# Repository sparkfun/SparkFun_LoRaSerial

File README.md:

SparkFun LoRaSerial
========================================

[*SparkFun LoRaSerial Kit - 915MHz (WRL-19311)*](https://www.sparkfun.com/products/19311)

Head to the [LoRaSerial Product Manual](http://docs.sparkfun.com/SparkFun_LoRaSerial/) for technical documentation.

LoRaSerial is a pair of serial radio modems that simply passes serial back and forth. Do you have a system that needs to report data every few seconds? Is it located beyond WiFi or Bluetooth range? Do you need 9 mile/15 kilometer range? LoRaSerial transmits data over LoRa giving it incredible range compared to other methods. We’ve regularly transmitted over 9 miles/15km line-of-sight using two LoRaSerial radios, right out of the box.

LoRaSerial utilizes a 1 watt 915MHz transceiver and an open source protocol to and transmit AES encrypted data at 4800bps or approximately 480 bytes per second. Video streaming, this is not. LoRaSerial is very good at getting whatever data you need from point A to point B, encrypted, without configuration. The radios automatically frequency hop (FHSS) between channels to avoid collisions. The ‘airspeed’ or data rate is configurable up to approximately 2,000 bytes per second for shorter range, or for *extremely* long range transmissions, as low as 400 bytes per second.

LoRaSerial radios support simple point to point and point as well as multipoint broadcasts. Multipoint broadcasting makes it ideal for GNSS RTK and many other scenarios where one device needs to produce data and many devices need to consume that data.

The LoRaSerial firmware supports an innovative and simple to use ‘training’ method. Pressing the train button on both radios will generate a new random network ID and AES encryption key and share them between radios. This makes pairing radios in the field as simple as a button press. WiFi WPS this is not. Bring the radios near each other and the LoRaSerial training method is simple and secure.

Currently, SparkFun is offering radios utilizing 915MHz modems that are allowed in most parts of the world. Please check your local restrictions. The radios are fully configurable to restrict frequencies, channels, dwell time, power output, and a variety of other settings to make the radios compatible with your local regulations.

Repository Contents
-------------------

* **/Binaries** - Compiled firmware, ready to load
* **/Documents** - Datasheets and additional product information
* **/Firmware** - Main Arduino firmware
* **/Hardware** - Eagle PCB files

Documentation
--------------

* **[LoRaSerial Product Manual](http://docs.sparkfun.com/SparkFun_LoRaSerial/)** - Configuration guide for the SparkFun LoRaSerial.

License Information
-------------------

This product is _**open source**_! 

Please review the LICENSE.md file for license information. 

If you have any questions or concerns on licensing, please contact technical support on our [SparkFun forums](https://forum.sparkfun.com/viewforum.php?f=152).

Distributed as-is; no warranty is given.

- Your friends at SparkFun.

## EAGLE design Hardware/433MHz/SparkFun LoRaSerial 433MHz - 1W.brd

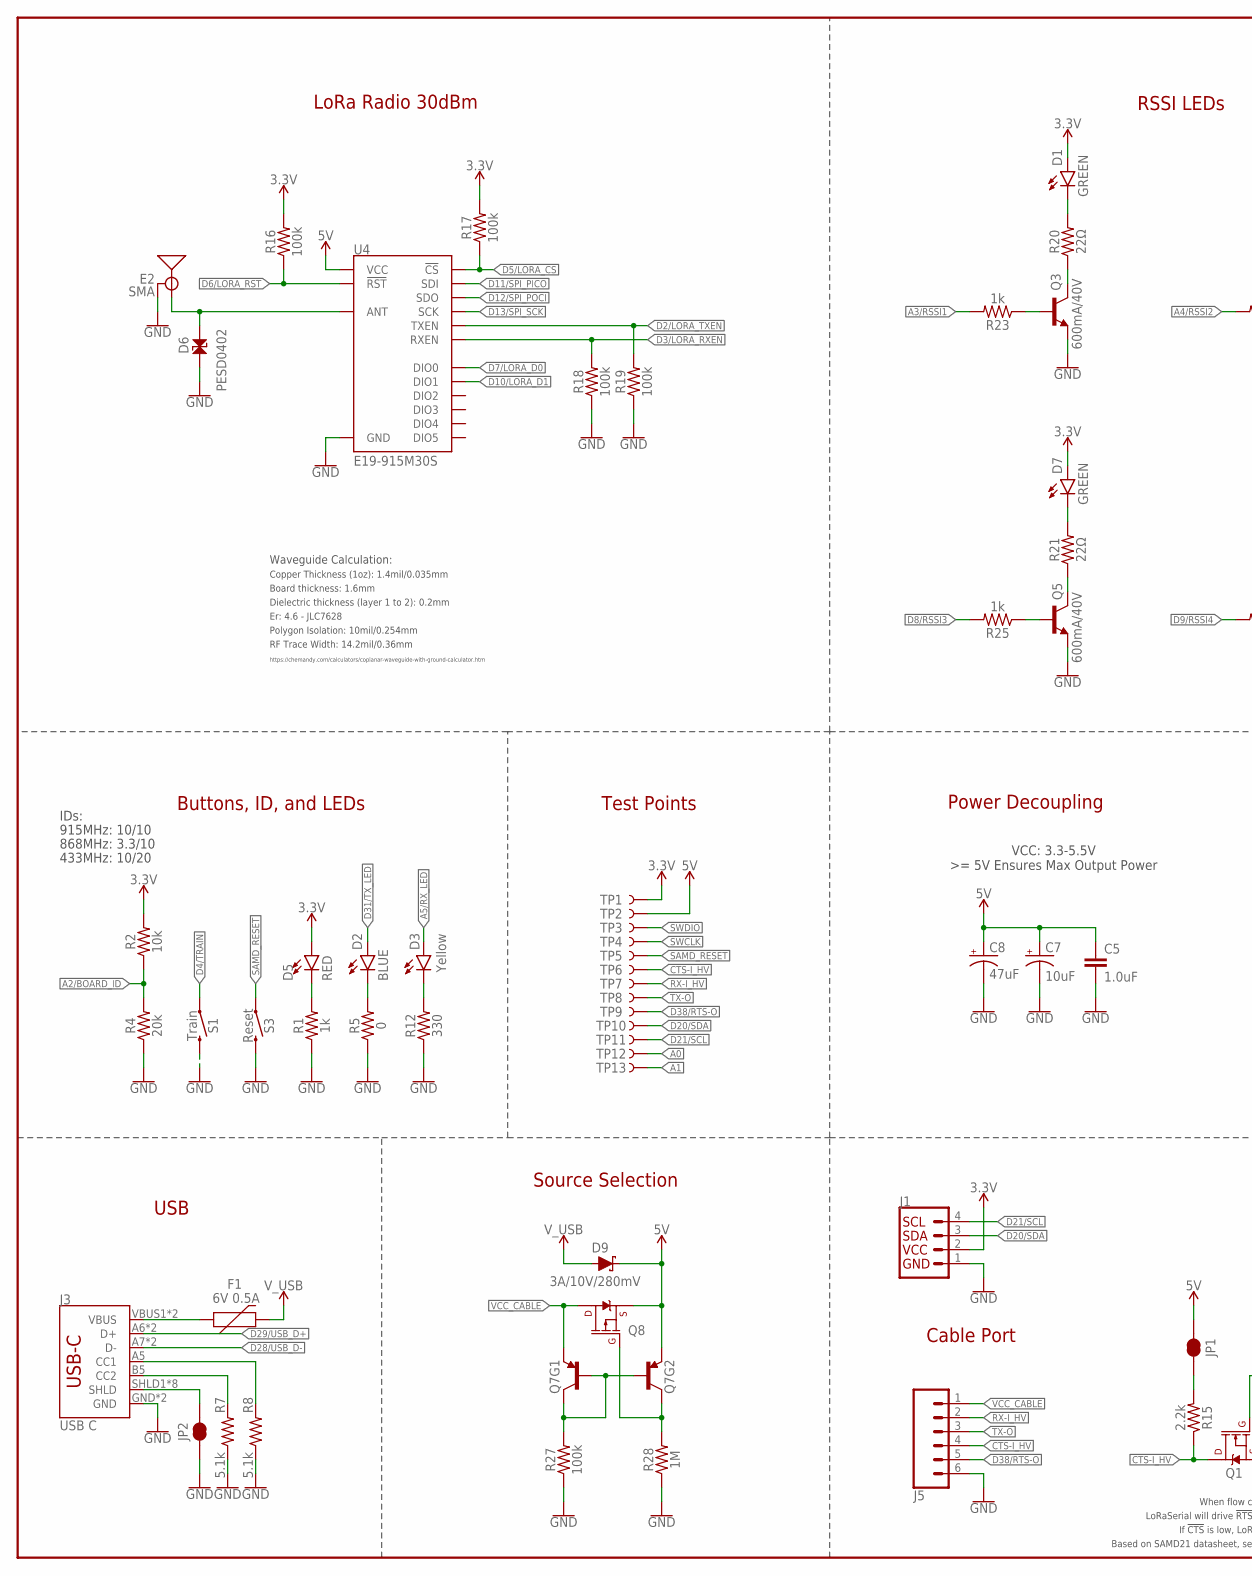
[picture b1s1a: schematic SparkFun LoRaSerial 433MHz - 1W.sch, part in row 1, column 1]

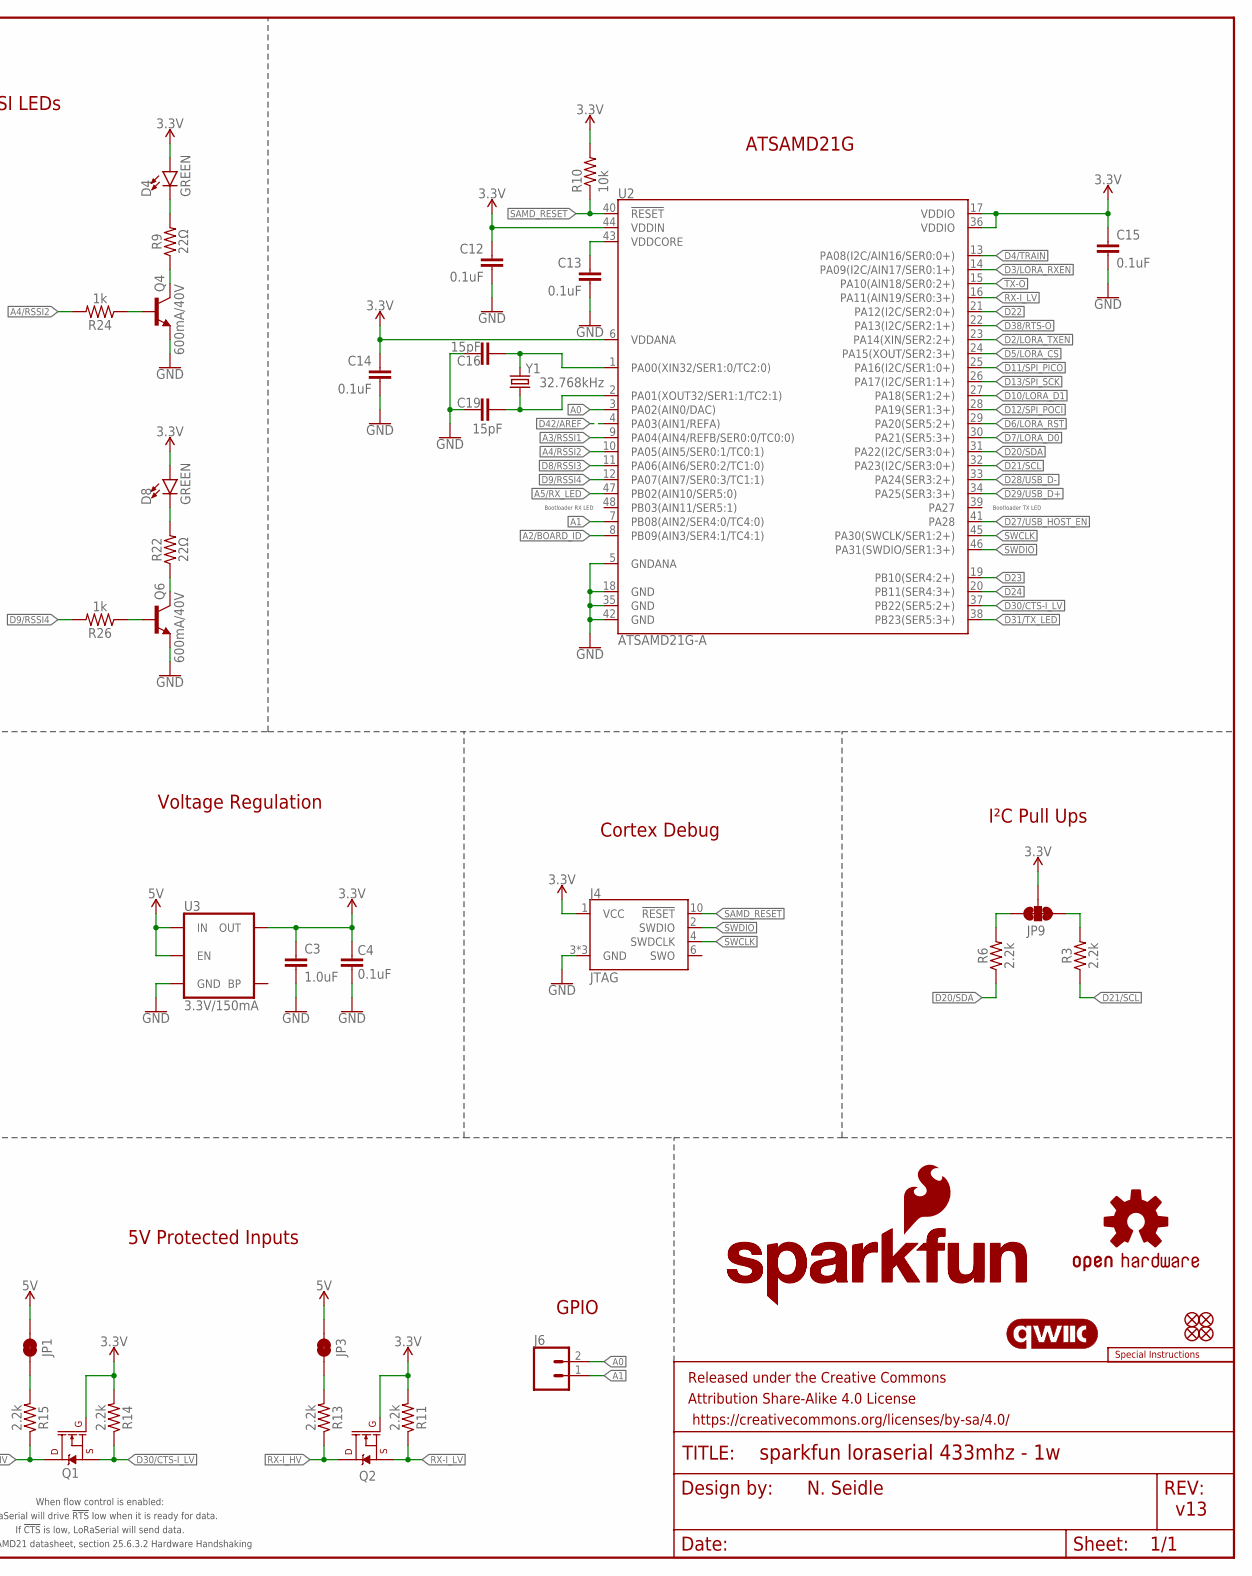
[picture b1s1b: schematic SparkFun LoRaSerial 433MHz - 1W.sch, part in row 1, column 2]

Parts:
C3, C5: 1.0uF; 0603
C4, C12, C13, C14, C15: 0.1uF; 0603
C7: 10uF; EIA3216
C8: 47uF; EIA3528
C16, C19: 15pF; 0603
D1, D4, D7, D8: GREEN; LED-0603
D2: BLUE; LED-0603
D3: Yellow; LED-0603
D5: RED; LED-0603
D6: PESD0402; 0402-TIGHT
D9: 3A/10V/280mV; SOD-323
E2: SMA; SMA-EDGE
F1: 6V 0.5A; 0805
FID1, FID2, FID3, FID4: FIDUCIAL1X2; FIDUCIAL-1X2
FRAME3: FRAME-LEDGER; CREATIVE_COMMONS
J1: QWIIC_RIGHT_ANGLE; JST04_1MM_RA
J3: USB C; USB-C-16P
J4: JTAG; 2X5-PTH-1.27MM-NO_SILK
J5: CONN_06JST-SMD-LOCKING; JST-6-SMD-1.25MM-LOCKING
J6: CONN_021X02_NO_SILK; 1X02_NO_SILK
JP1, JP2, JP3: JUMPER-SMT_2_NC_TRACE_SILK; SMT-JUMPER_2_NC_TRACE_SILK
JP9: JUMPER-SMT_3_2-NC_TRACE_SILK; SMT-JUMPER_3_2-NC_TRACE_SILK
LOGO1: SPECIAL_INSTRUCTIONS-ORDERING; ORDERING_INSTRUCTIONS
LOGO2: SFE_LOGO_NAME_FLAME9_MM; SFE_LOGO_NAME_FLAME_9MM
LOGO3: QWIIC_LOGO_CONNECTOR; QWIIC_5.5MM
LOGO4: OSHW-LOGOMINI; OSHW-LOGO-MINI
LOGO5: SFE_LOGO_NAME9_MM; SFE_LOGO_NAME_9MM
Q1, Q2: 20V/0.2A/8MHz/1.2Ω/1Vth; SOT-416FL
Q3, Q4, Q5, Q6: 600mA/40V; SOT23-3
Q7: TRANS_PNP_DUALSOT-363; SOT363_PHILIPS
Q8: 20V/4.2A/52mΩ/1.4W; SOT23-3
R1, R23, R24, R25, R26: 1k; 0603
R2, R10: 10k; 0603
R3, R6, R11, R13, R14, R15: 2.2k; 0603
R4: 20k; 0603
R5: 0; 0603
R7, R8: 5.1k; 0603
R9, R20, R21, R22: 22Ω; 0603
R12: 330; 0603
R16, R17, R18, R19, R27: 100k; 0603
R28: 1M; 0603
S1: Train; TACTILE_SWITCH_SMD_RIGHT_ANGLE
S3: Reset; TACTILE_SWITCH_SMD_5.2MM
TP1, TP2, TP3, TP4, TP5, TP6, TP7, TP8, TP9, TP10, TP11, TP12, TP13: TEST-POINT3X5; PAD.03X.05
U2: ATSAMD21G-A; TQFP-48
U3: 3.3V/150mA; SOT23-5
U4: E19-915M30S; E19-433M30S
Y1: 32.768kHz; CRYSTAL-SMD-3.2X1.5MM

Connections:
3.3V: C3.1, C4.2, C12.1, C14.1, C15.1, D1.A, D4.A, D5.A, D7.A, D8.A, J1.2, J4.1 (VCC), JP9.2, Q1.1 (G), Q2.1 (G), R2.2, R10.2, R11.2, R14.2, R16.2, R17.2, TP1.1, U2.6 (VDDANA), U2.17 (VDDIO), U2.36 (VDDIO), U2.44 (VDDIN), U3.5 (OUT)
5V: C5.1, C7.+, C8.A (+), D9.C, JP1.2, JP3.2, Q7.4 (E), Q8.2 (S), TP2.1, U3.1 (IN), U3.3 (EN), U4.11 (VCC)
!CTS!-I_HV: J5.4, Q1.3 (D), R15.1, TP6.1
A0: J6.2, TP12.1, U2.3 (PA02(AIN0/DAC))
A1: J6.1, TP13.1, U2.7 (PB08(AIN2/SER4:0/TC4:0))
A2/BOARD_ID: R2.1, R4.2, U2.8 (PB09(AIN3/SER4:1/TC4:1))
A3/RSSI1: R23.2, U2.9 (PA04(AIN4/REFB/SER0:0/TC0:0))
A4/RSSI2: R24.2, U2.10 (PA05(AIN5/SER0:1/TC0:1))
A5/RX_LED: D3.A, U2.47 (PB02(AIN10/SER5:0))
CC1: J3.A5 (CC1), R8.2
CC2: J3.B5 (CC2), R7.2
D2/LORA_TXEN: R19.2, U2.23 (PA14(XIN/SER2:2+)), U4.16 (TXEN)
D3/LORA_RXEN: R18.2, U2.14 (PA09(I2C/AIN17/SER0:1+)), U4.17 (RXEN)
D4/TRAIN: S1.1, U2.13 (PA08(I2C/AIN16/SER0:0+))
D5/LORA_!CS!: R17.1, U2.24 (PA15(XOUT/SER2:3+)), U4.15 (!CS)
D6/LORA_!RST!: R16.1, U2.29 (PA20(SER5:2+)), U4.8 (!RST)
D7/LORA_D0: U2.30 (PA21(SER5:3+)), U4.7 (DIO0)
D8/RSSI3: R25.2, U2.11 (PA06(AIN6/SER0:2/TC1:0))
D9/RSSI4: R26.2, U2.12 (PA07(AIN7/SER0:3/TC1:1))
D10/LORA_D1: U2.27 (PA18(SER1:2+)), U4.6 (DIO1)
D11/SPI_PICO: U2.25 (PA16(I2C/SER1:0+)), U4.14 (SDI)
D12/SPI_POCI: U2.28 (PA19(SER1:3+)), U4.13 (SDO)
D13/SPI_SCK: U2.26 (PA17(I2C/SER1:1+)), U4.12 (SCK)
D20/SDA: J1.3, R6.1, TP10.1, U2.31 (PA22(I2C/SER3:0+))
D21/SCL: J1.4, R3.1, TP11.1, U2.32 (PA23(I2C/SER3:0+))
D22: U2.21 (PA12(I2C/SER2:0+))
D23: U2.19 (PB10(SER4:2+))
D24: U2.20 (PB11(SER4:3+))
D27/USB_HOST_EN: U2.41 (PA28)
D28/USB_D-: J3.A7 (D-), J3.B7 (D-), U2.33 (PA24(SER3:2+))
D29/USB_D+: J3.A6 (D+), J3.B6 (D+), U2.34 (PA25(SER3:3+))
D30/!CTS!-I_LV: Q1.2 (S), R14.1, U2.37 (PB22(SER5:2+))
D31/TX_LED: D2.A, U2.38 (PB23(SER5:3+))
D38/!RTS!-O: J5.5, TP9.1, U2.22 (PA13(I2C/SER2:1+))
D42/AREF: U2.4 (PA03(AIN1/REFA))
GND: C3.2, C4.1, C5.2, C7.-, C8.C (-), C12.2, C13.2, C14.2, C15.2, C16.1, C19.2, D6.1, E2.GND@0 (GND), E2.GND@1 (GND), E2.GND@2 (GND), E2.GND@3 (GND), J1.1, J3.GND, J3.GND2 (GND), J4.3 (GND), J4.5 (GND), J4.9 (GND), J5.6, JP2.1, Q3.2 (E), Q4.2 (E), Q5.2 (E), Q6.2 (E), R1.1, R4.1, R5.1, R7.1, R8.1, R12.1, R18.1, R19.1, R27.1, R28.1, S1.2, S3.3 (2), S3.4 (2), U2.5 (GNDANA), U2.18 (GND), U2.35 (GND), U2.42 (GND), U3.2 (GND), U4.1 (GND), U4.9 (GND), U4.10 (GND), U4.18 (GND), U4.20 (GND), U4.21 (GND), U4.22 (GND)
LORA_ANT: D6.2, E2.SIG (SIGNAL), U4.19 (ANT)
unnamed: C19.1, U2.2 (PA01(XOUT32/SER1:1/TC2:1)), Y1.P$1 (1)
unnamed: C16.2, U2.1 (PA00(XIN32/SER1:0/TC2:0)), Y1.P$2 (2)
unnamed: D3.C, R12.2
unnamed: D2.C, R5.2
unnamed: JP3.1, R13.2
unnamed: JP1.1, R15.2
unnamed: D5.C, R1.2
unnamed: D4.C, R9.2
unnamed: D1.C, R20.2
unnamed: D7.C, R21.2
unnamed: D8.C, R22.2
unnamed: Q3.3 (C), R20.1
unnamed: Q3.1 (B), R23.1
unnamed: Q4.3 (C), R9.1
unnamed: Q4.1 (B), R24.1
unnamed: Q5.3 (C), R21.1
unnamed: Q5.1 (B), R25.1
unnamed: Q6.3 (C), R22.1
unnamed: Q6.1 (B), R26.1
unnamed: J3.SHLD1 (SHLD), J3.SHLD2 (SHLD), J3.SHLD3 (SHLD), J3.SHLD4 (SHLD), J3.SHLD5 (SHLD), J3.SHLD6 (SHLD), J3.SHLD7 (SHLD), J3.SHLD8 (SHLD), JP2.2
unnamed: Q7.3 (C), Q8.1 (G), R28.2
unnamed: Q7.2 (B), Q7.5 (B), Q7.6 (C), R27.2
RX-I_HV: J5.2, Q2.3 (D), R13.1, TP7.1
RX-I_LV: Q2.2 (S), R11.1, U2.16 (PA11(AIN19/SER0:3+))
SAMD_!RESET!: J4.10 (!RESET), R10.1, S3.1, S3.2 (1), TP5.1, U2.40 (!RESET!)
SCL_PU1: JP9.1, R3.2
SDA_PU1: JP9.3, R6.2
SWCLK: J4.4 (SWDCLK), TP4.1, U2.45 (PA30(SWCLK/SER1:2+))
SWDIO: J4.2 (SWDIO), TP3.1, U2.46 (PA31(SWDIO/SER1:3+))
TX-O: J5.3, TP8.1, U2.15 (PA10(AIN18/SER0:2+))
VCC_CABLE: J5.1, Q7.1 (E), Q8.3 (D)
VDDCORE: C13.1, U2.43 (VDDCORE)
VUSB: F1.1, J3.VBUS1 (VBUS), J3.VBUS2 (VBUS)
V_USB: D9.A, F1.2

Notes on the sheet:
v13
Cable Port
Voltage Regulation
N. Seidle
LoRa Radio 30dBm
Power Decoupling
VCC: 3.3-5.5V >= 5V Ensures Max Output Power
Board thickness: 1.6mm
Er: 4.6 - JLC7628
Copper Thickness (1oz): 1.4mil/0.035mm
RF Trace Width: 14.2mil/0.36mm
Polygon Isolation: 10mil/0.254mm
Dielectric thickness (layer 1 to 2): 0.2mm
https://chemandy.com/calculators/coplanar-waveguide-with-ground-calculator.htm
Waveguide Calculation:
USB
ATSAMD21G
5V Protected Inputs
Cortex Debug
Bootloader TX LED
Bootloader RX LED
GPIO
Buttons, ID, and LEDs
I²C Pull Ups
RSSI LEDs
Test Points
Source Selection
IDs:
915MHz: 10/10
868MHz: 3.3/10
433MHz: 10/20
LoRaSerial will drive !RTS! low when it is ready for data.
If !CTS! is low, LoRaSerial will send data.
Based on SAMD21 datasheet, section 25.6.3.2 Hardware Handshaking
When flow control is enabled:

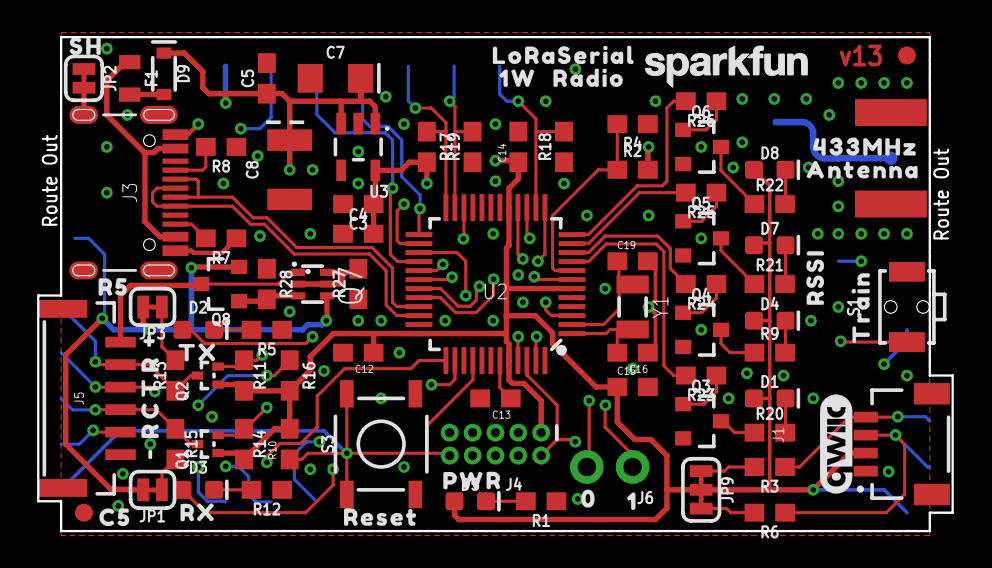
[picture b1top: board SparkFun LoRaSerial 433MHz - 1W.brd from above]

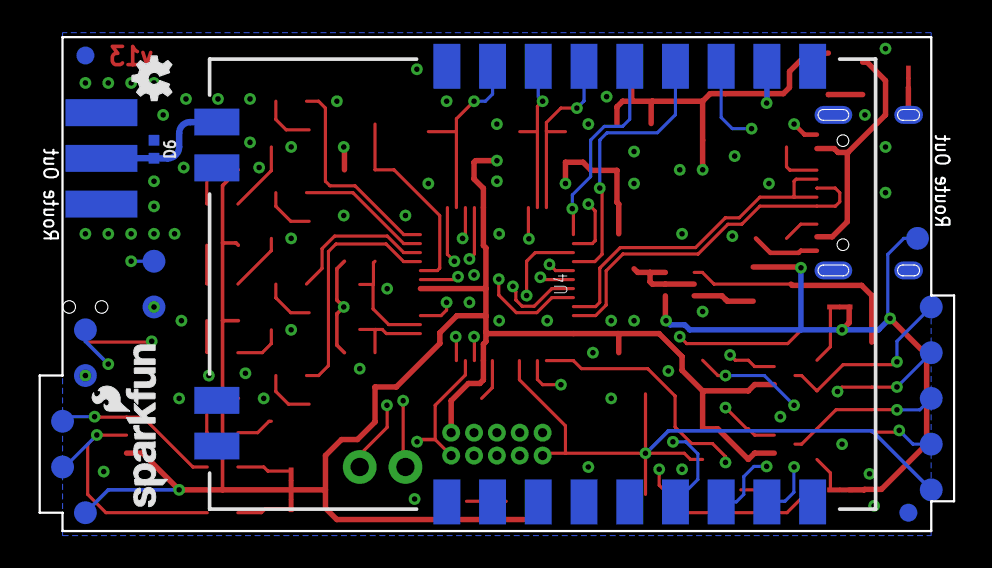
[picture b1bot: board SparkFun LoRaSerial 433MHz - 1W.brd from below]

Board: 4 copper layers, 50.8 x 27.4 mm, 118 parts (20 on the bottom side), 66 nets.

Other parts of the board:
U$1: 1W1
U$2: RESET0
U$4: TRAIN0
U$5: RADIO2
U$6: 01
U$7: PWR0
U$8: 433MHZ0
U$9: ANTENNA1
U$10: RX1
U$11: TX0
U$12: #0
U$13: #1
U$14: R3
U$15: T2
U$16: C0
U$17: R1
U$18: LORASERIAL0
U$19: C50
U$20: R50
U$21: RSSI0
U$22: 10
U$23: SH0

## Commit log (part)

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2023-01-03 Add mSecToChannelZero to compute the time remaining until reaching CH-0
2023-01-03 Update channelTimerStart in syncChannelTimer
2023-01-03 Verify the channelTimer value when building the TX header
2023-01-03 DO NOT MERGE: Channel timer verification .vs. old code
2023-01-06 Always reload the channel timer in the ISR
2023-01-06 Update the trigger names and code locations
    Please leave the trigger list alphabetized.
    Add and remove name only.
    Reorganize for debugging, but DON'T check in the changes for debugging!
2023-01-07 Compute the retransmit timeout (backoff) in retransmitDatagram
2023-01-07 Clear timeToHop when delaying the hop
2023-01-07 Fix the case when both the remote and local values are negative
2023-01-07 Stop the channel timer when the P2P link is down
2023-01-09 Add the timestamp to link up and link down display
2023-01-09 Add channelTimer history
2023-01-09 Compute the transmit times for SYNC_CLOCKS, HEARTBEAT and DATA_ACK
2023-01-09 Rename FrameTimeout to SerialDelay and move to serial settings
2023-01-09 Describe the steps to prevent attacks on the LoRaSerial network
2023-01-09 Display the ACK, HEARTBEAT and SYNC_CLOCKS transmit times with ATI10
2023-01-09 Add virtual-circuit triggers for TX and RX
2023-01-09 Add DATA_ACK, HEARTBEAT and SYNC_CLOCKS air time in mSec to SYNC_CLOCKS
2023-01-11 Typo fix
2023-01-11 Rename txSyncClockUsec to txSyncClocksUsec
2023-01-12 Transmit ignore frames to get TX times for SYNC_CLOCKS, HEARTBEAT, ACK
2023-01-12 VC: Fix the timestamp offset calculations
2023-01-12 VC: Remove dead code
2023-01-12 Multipoint: Use the measured TX times for channel timer synchronization
2023-01-12 P2P: Fix error in link down/up synchronization
2023-01-12 Fix wrap around test
2023-01-13 VcServerTest: Turn off the debugging and ACKs
2023-01-13 P2P: Add point-to-point LED pattern
2023-01-13 Display the case number in syncChannelTimer when debugSync is enabled
2023-01-13 P2P: Use transmit measurements for syncChannelTimer calcualtions
2023-01-13 Set verifyRxNetID to true by default
2023-01-17 Display the command which received the error
2023-01-17 Update the VcServerTest application
    Integrate changes from SprinklerServer
2023-01-17 Set txSetChannelTimerMicros even when frequencyHop is false
    Enable the proper calculation of TX time for the various frames
2023-01-21 Whitespace changes
2023-01-21 Remove extra triggers
2023-01-21 VcServerTest: Display unknown VC messages received from the radio
2023-01-23 Blink error LED and regularly output an error message
    Add an error message to waitForever
2023-01-23 Add channelNumber move to MP linkup
2023-01-23 Move dumpClockSynchronization() within debug guard
2023-01-23 Remove channelNumber update from HEARTBEAT recv.
2023-01-23 Use Modem Clear and RX On-going for receiveInProcess
2023-01-23 Add comment
2023-01-24 MP: Remove display of uninitialized variable
2023-01-26 Fix developer guards
2023-01-26 Fix bug in return of getReceiveCompletionOffset
2023-01-28 Fix calcAirTime to use LDRO and Implicit header.
2023-01-28 Allow msToNextHop to be negative
2023-01-29 VC: Send command complete to the PC
2023-01-29 VC: Properly return command status to remote system's host
2023-01-29 VcServerTest: Wait for command execution
2023-01-30 Replace TX_TO_RX_USEC with settings.txToRxUsec
2023-01-30 Set txToRxUsec based upon airSpeed
2023-01-30 Compute the time delay to the next HEARTBEAT transmission
    The HEARTBEAT frame to be received within the heartbeatTimeout period.
2023-01-30 Add timeoutMsec to compute the timeout delay
2023-01-30 Replace maxPacketAirTime with maxFrameAirTimeMsec
2023-01-30 Properly initialize the heartbeat timeout during RADIO_RESET
2023-01-30 Replace frameAirTime with frameAirTimeUsec
2023-01-30 Whitespace formatting changes
2023-01-31 Define and use NEXT_COMMAND_TX_TAIL macro
2023-01-31 Output a line at a time in dumpCircularBuffer
2023-01-31 Display the bytes placed into outgoingPacket
2023-01-31 VC: Ensure the entire command complete message is contained in one frame
2023-01-31 Sprinkler Controller: Set the default setting values
2023-01-31 Sprinkler Controller: Add I2C support
2023-01-31 Sprinkler Controller: Add the global variables
2023-01-31 Sprinkler Controller: Add new command types
2023-01-31 Sprinkler Controller: Update time of day
2023-01-31 Sprinkler Controller: Add the test script
2023-01-31 VcServerTest: Enable/disable DISPLAY_UNKNOWN_COMMANDS
2023-01-31 Fix typo
2023-01-31 Revert settings.h
2023-02-01 Revert "VcServerTest: Enable/disable DISPLAY_UNKNOWN_COMMANDS"
2023-02-06 Adjust heartbeatTimeout depending upon airSpeed
2023-02-06 Add some virtual circuit documentation
2023-02-06 Make tool windows compatible
2023-02-06 Fix the link to Virtual_Circuits.md
2023-02-08 Get the cylon pattern to display during training
2023-02-08 Adding compile action
2023-02-09 VC: Add more example code documentation
2023-02-09 Github Action - Updating Binary Feb 09 2023
2023-02-09 Clean up binary programming folder
2023-02-10 Temp rename
2023-02-12 Document LoRaSerial radio training
2023-02-13 Docs update
2023-02-13 Add improvements for low air-speeds
2023-02-13 Add channel number to MP HB
    Channel number needed for Client link up
2023-02-13 Increase MP_HEARTBEAT_BYTES / Add Channel Number
2023-02-13 Move to MP Standby if discovery fails
2023-02-13 Remove redundant code
2023-02-13 Github Action - Updating Binary Feb 13 2023
2023-02-13 Update programming tools
2023-02-14 Update handling of settings during command mode and training
2023-02-14 Fix wrap-around on debugSerial prints
2023-02-15 Remove old binaries
2023-02-15 Update AT commands
2023-02-15 Update docs
2023-02-16 Training: Remove switch to server from client
2023-02-16 Update flow control notes
2023-02-17 Rename the LED pins to use the color and number
2023-02-18 Intro: Update the introduction to point at the quick start guide
2023-02-18 Update the LED documentation
2023-02-21 Add kit images
2023-02-22 Rename index.md
2023-02-22 Docs: Add RTT remote command
2023-02-22 Fix link
2023-02-24 Pass settings address to generateRandomKeysID
2023-02-24 Use a common reset function
2023-02-24 Make the callers set trainingSettings
2023-02-24 Update the training and LED documents for the new training bahavior
2023-03-01 Reduce times for training and factory reset.
2023-03-01 Immediately do system reset if train button triggers factory defaults
2023-03-01 Squelch RSSI until link is up.
2023-03-01 Remove old RCs from combined directory.
2023-03-04 Remove virtual circuit documentation from version 2.0
2023-03-05 Fix the backspace in command mode
2023-03-05 Fix flow control and add ATI50 command to test it
2023-03-06 Improve remote command processing, add more serial debugging
2023-03-06 Add the virtual circuit support
2023-03-06 Remove unnecessary files from Tools
2023-03-06 Fix serialTransmitBuffer overrun - drain buffer when it gets full
2023-03-07 Add power usage docs
2023-03-07 Add info on power output during training
2023-03-07 Lock SAMD platform version
2023-03-07 Move virtual circuit commands to ATI3x and SX register display to ATI51
2023-03-09 Add enclosure information
2023-03-10 Remove old fix
2023-03-10 Github Action - Updating Binary Mar 10 2023
2023-03-12 Allow white space in the command
    Valid commands may now include space, horizontal tab(0x09), line feed
    (0x0a), vertical tab (0x0b), form feed (0x0c) and are terminated with a
    carriage return (0x0d). These characters are removed prior to
    processing the command.
    Blank lines return OK.
    Valid commands:
2023-03-13 Always return to PRINT_TO_SERIAL at the end of a command
2023-03-13 Bug Fix: Receive remote command responses when in command mode
2023-03-13 Only start one command at a time
2023-03-13 Process the command as soon as it fills the command buffer
2023-03-13 VC: Change APIs for test routines
2023-03-13 Add Slow_Read application to test flow control
2023-03-13 Update images and docs to v13 hardware
2023-03-17 VCT: BUG FIX - PC command queue type
2023-03-17 VCT: Use proper VC commands, remove some sprinkler server stuff
2023-03-17 VCT: Reduce stall check from 15 seconds to 5 seconds
2023-03-17 VCT: BUG FIX - Only complete the ATC command when the VC is connected
2023-03-17 VCT: Properly handle embedded VC messages in the remote command response
2023-03-18 Update power table and average current.
2023-03-21 Add the virtual circuit documentation
2023-03-24 MP: Don't change state when not necessary
2023-03-24 MP: Stop the channel clock while waiting for HEARTBEAT on channel 0
2023-03-24 Add LDRO config. Add airspeed lookup.
2023-03-24 Display airspeed during command mode
2023-04-02 VCT: Validate the srcVC before indexing the virtualCircuitList
2023-04-02 VC: Add ATI33 command to display the VC states
2023-04-10 VCT: Properly order the output by emptying buffered output
2023-04-10 VCT: Stop the command processor when the VC link fails
2023-04-10 VCT: Bug fix - Properly wait until the PC commnd processor is idle
2023-04-10 VCT: Properly stop the command processors
2023-04-13 Transmit channel number in header for hop and channel synchronization
    Use channel number during hop timer synchronization to determine the
    current channel.
2023-04-15 Separate the default settings from the values in settings.h
2023-04-16 Make operating mode and airSpeed easy to change
    Move airSpeed values into a table.
    Verify the airSpeed table against the enum values
    Load the default values anytime the EEPROM is erased
    Add preamble to air speed values
2023-08-13 Display the decoded SAMD21 BOD33 register value
2023-09-03 Update makefile to build LoRaSerial using the Arduino CLI
2023-12-07 Add link from Operating mode page to AT commands.
2023-12-28 Fix typo and rearrange docs.
2023-12-28 Pin mkdocs version to avoid error
2023-12-28 Deployed 62aa9cc with MkDocs version: 1.5.3
2024-02-16 Fix CRC error detection
2024-02-16 Add end of if comments
2024-02-17 Update petWDT, define PET_TIMEOUT and move lastPet into petWDT
2024-02-17 Only output serial data when some placed in the buffer
2024-02-17 Add module identification and routine separation
2024-02-25 Fix case for CheckChannelHop and remove checkChannelHopAndKickWatchdog
2024-02-25 Move channelTimerHandler into Radio.ino
2024-02-25 Add mid level radio routines
    Add routines between the LoRaSerial logic and the calls to RadioLib that
    use SPI to interface with the LoRa radio.
2024-02-25 Add inInterruptRoutine parameter to radioSetFrequency, setRadioFrequency

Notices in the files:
parts and their libraries:
SparkFun-Aesthetics: Licensing: Creative Commons ShareAlike 4.0 International - https://creativecommons.org/licenses/by-sa/4.0
SparkFun-LED: Licensing: CC v3.0 Share-Alike You are welcome to use this library for commercial purposes.
SparkFun-Aesthetics: Released under the Creative Commons
